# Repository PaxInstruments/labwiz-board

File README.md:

# Pax Instruments
# armwiz-board

[Pax Instruments Template Module](<link to store page>)

## Overview
The Pax Instruments armwiz board is a development board based on the STM32 series processors specifically targeting the STM32F103RxT series. You can [purchase this item in our store](http://paxinstruments.com/products/).

## Repository Contents
- __Datasheets__ - Datasheets for relevant components and parts
- __Electronics__ - All PCB and schematic design files
- __Enclosure__ - Enclosure 3D design files
- __Firmware__ - Firmware, libraries, and examples
- __Production__ - Manufacturing resources
- __Resources__ - Other resources

## Product Versions

## License Information
```
Place the license statement here
```

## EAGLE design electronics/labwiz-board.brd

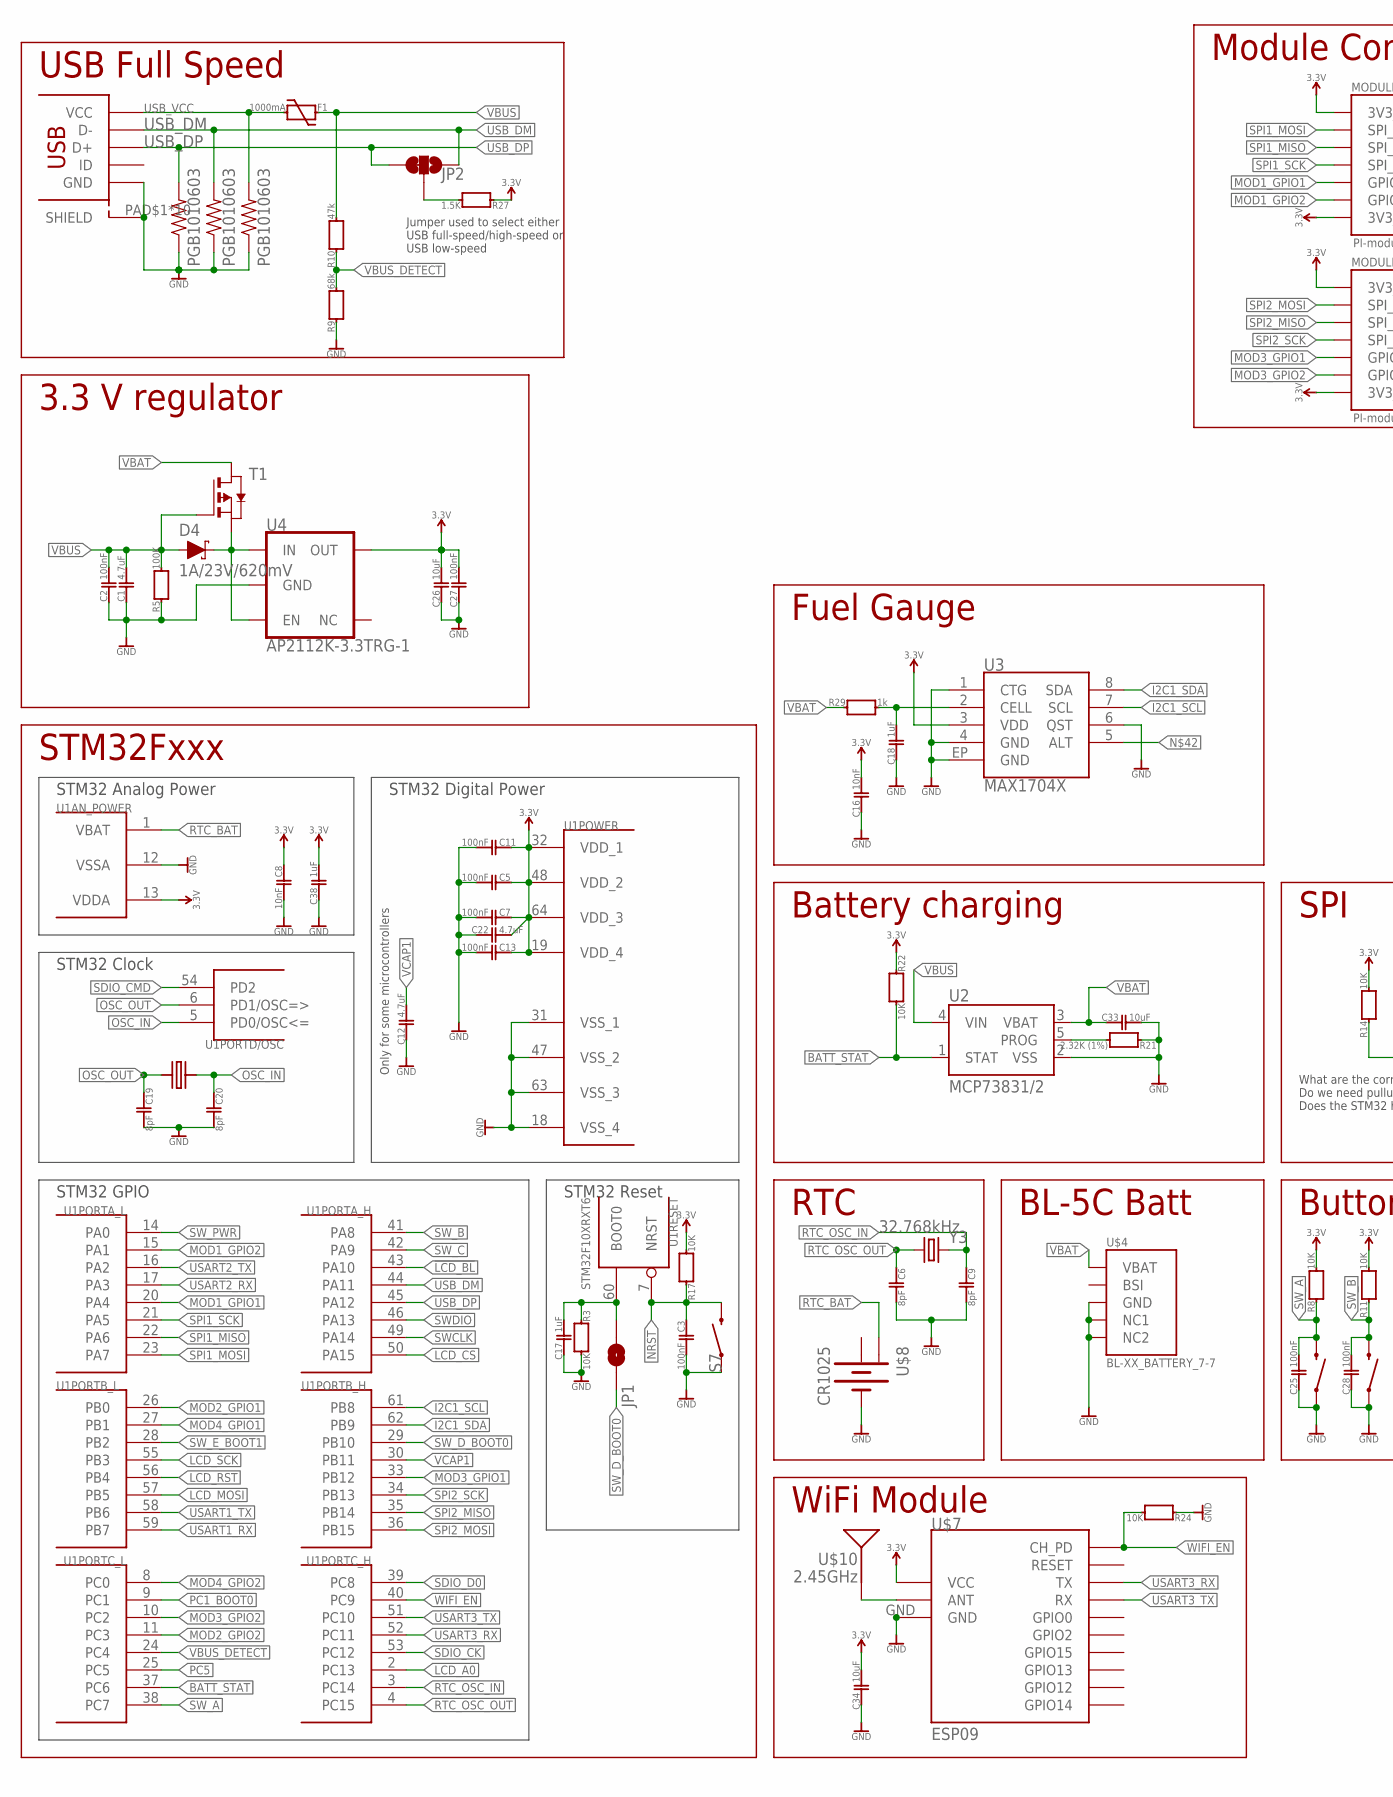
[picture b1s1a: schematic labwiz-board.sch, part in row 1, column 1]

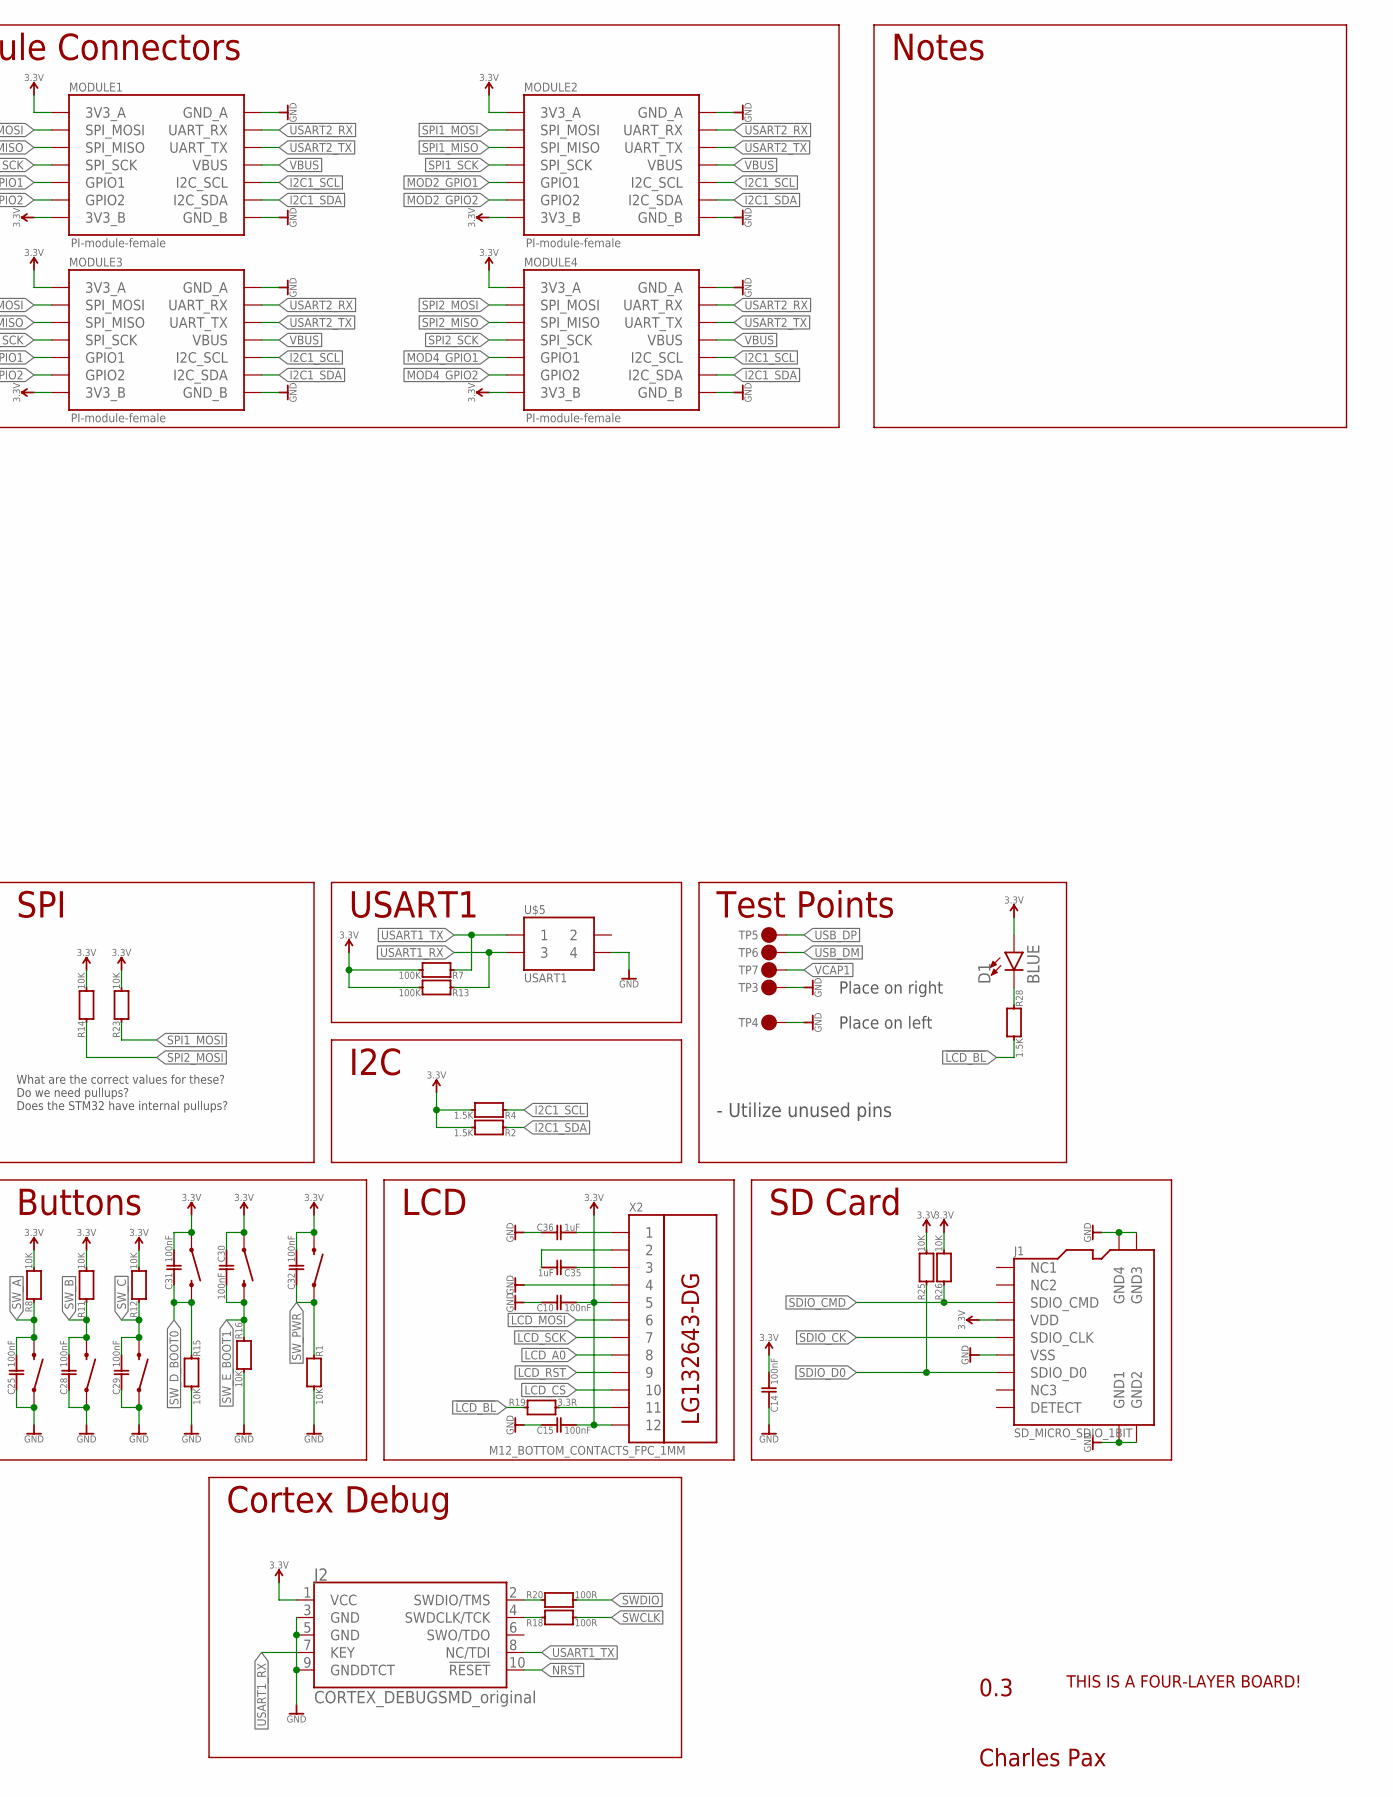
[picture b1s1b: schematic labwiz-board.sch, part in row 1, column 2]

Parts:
C1, C12, C22: 4.7uF; 0402
C2, C3, C5, C7, C10, C11, C13, C14, C15, C25, C27, C28, C29, C30, C31, C32: 100nF; 0402
C6, C9, C19, C20: 8pF; 0402
C8, C16: 10nF; 0402
C17, C18, C35, C36, C38: 1uF; 0402
C26, C33, C34: 10uF; 0402
D1: BLUE; LED-0603
D4: 1A/23V/620mV; SOD-323
F1: 1000mA; 0805
J1: SD_MICRO_SDIO_1BIT; SD_MICRO_1
J2: CORTEX_DEBUGSMD_original; SAMTECH_FTSH-105-01
JP1: DNP; PAD-JUMPER-2-NO_YES_SILK
JP2: JUMPER-SMT_3_1-NC_TRACE_SILK; SMT-JUMPER_3_1-NC_TRACE_SILK
MODULE1, MODULE2, MODULE3, MODULE4: PI-module-female; M07X2_2MM_EDGE
R1, R3, R8, R11, R12, R14, R15, R16, R17, R22, R23, R24, R25, R26: 10K; 0402
R2, R4, R27, R28: 1.5K; 0402
R5, R7, R13: 100K; 0402
R9: 68k; 0402
R10: 47k; 0402
R18, R20: 100R; 0402
R19: 3.3R; 0402
R21: 2.32K (1%); 0402
R29: 1k; 0402
S1, S2, S3, S4, S5, S6: SWITCH-MOMENTARY-2SMD; TACTILE_SWITCH_SMD; MPN RS-187R05A2-DS MT RT
S7: SWITCH-MOMENTARY-2SMD-3; TACTILE_SWITCH_SMD-3
T1: PMOSSOT23-6; SOT23-6
TP3, TP4: DNP; M01_TH
TP5, TP6, TP7: DNP; PAD_1MM
U1: STM32F10XRXT6; TQFP64
U2: MCP73831/2; SOT23-5
U3: MAX1704X; TDFN-8
U4: AP2112K-3.3TRG-1; SOT23-5
U$1: USB_MICROSMT+THRUHULE; USB_MICRO_THRUHOLE; MPN 10118194-0001LF
U$2: DNP; FOUR_LAYER_WARNING
U$3: LG132643-DG
U$4: BL-XX_BATTERY_7-7; BL-XX-BATTERY
U$5: USART1; M02X2_TH_RIGHT_ANGLE
U$7: ESP09
U$8: CR1025; CR2025
U$9: 8MHz; NX3225GD
U$10: 2.45GHz; ANT-2.4GHZ-6.5X2.2MM
X2: M12_BOTTOM_CONTACTS_FPC_1MM; FPC_12P_1MM
Y3: 32.768kHz; CRYSTAL-SMD-3.2X1.5MM
Z1, Z2, Z3: PGB1010603; SPARKFUN-RESISTORS_0603-RES; MPN PGB1010603NRHF

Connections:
3.3V: C5.1, C7.1, C8.1, C10.2, C11.1, C13.1, C14.2, C15.2, C16.2, C22.2, C26.2, C27.2, C30.1, C31.2, C32.2, C34.2, C38.2, D1.A, J1.4 (VDD), J2.1 (VCC), MODULE1.P$1 (3V3_A), MODULE1.P$13 (3V3_B), MODULE2.P$1 (3V3_A), MODULE2.P$13 (3V3_B), MODULE3.P$1 (3V3_A), MODULE3.P$13 (3V3_B), MODULE4.P$1 (3V3_A), MODULE4.P$13 (3V3_B), R2.1, R4.1, R7.1, R8.1, R11.1, R12.1, R13.1, R14.1, R17.1, R22.2, R23.1, R25.1, R26.1, R27.2, S4.1, S5.1, S6.3 (2), U1.13 (VDDA), U1.19 (VDD_4), U1.32 (VDD_1), U1.48 (VDD_2), U1.64 (VDD_3), U3.3 (VDD), U4.5 (OUT), U$7.VCC, X2.5, X2.12
!LCD_BL: R19.2, R28.1, U1.43 (PA10)
+: U$8.P$2 (+)
BATT_STAT: R22.1, U1.37 (PC6), U2.1 (STAT)
GND: C1.1, C2.1, C3.2, C5.2, C6.2, C7.2, C8.2, C9.2, C10.1, C11.2, C12.1, C13.2, C14.1, C15.1, C16.1, C17.1, C18.1, C19.2, C20.2, C22.1, C25.1, C26.1, C27.1, C28.1, C29.1, C33.2, C34.1, C36.1, C38.1, J1.6 (VSS), J1.G1 (GND1), J1.G2 (GND2), J1.G3 (GND3), J1.G4 (GND4), J2.3 (GND), J2.5 (GND), J2.9 (GNDDTCT), MODULE1.P$2 (GND_A), MODULE1.P$14 (GND_B), MODULE2.P$2 (GND_A), MODULE2.P$14 (GND_B), MODULE3.P$2 (GND_A), MODULE3.P$14 (GND_B), MODULE4.P$2 (GND_A), MODULE4.P$14 (GND_B), R1.1, R3.1, R5.2, R9.2, R15.1, R16.1, R21.2, R24.2, S1.1, S2.1, S3.1, S7.1, TP3.P$1, TP4.P$1, U1.12 (VSSA), U1.18 (VSS_4), U1.31 (VSS_1), U1.47 (VSS_2), U1.63 (VSS_3), U2.2 (VSS), U3.1 (CTG), U3.4 (GND), U3.6 (QST), U3.EP (GND), U4.2 (GND), U$1.PAD$1 (SHIELD), U$1.PAD$2 (SHIELD), U$1.PAD$3 (SHIELD), U$1.PAD$4 (SHIELD), U$1.PAD$5 (SHIELD), U$1.PAD$6 (SHIELD), U$1.PAD$7 (SHIELD), U$1.PAD$8 (SHIELD), U$1.PAD$9 (SHIELD), U$1.PAD$10 (SHIELD)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
I2C1_SCL: MODULE1.P$10 (I2C_SCL), MODULE2.P$10 (I2C_SCL), MODULE3.P$10 (I2C_SCL), MODULE4.P$10 (I2C_SCL), R4.2, U1.61 (PB8), U3.7 (SCL)
I2C1_SDA: MODULE1.P$12 (I2C_SDA), MODULE2.P$12 (I2C_SDA), MODULE3.P$12 (I2C_SDA), MODULE4.P$12 (I2C_SDA), R2.2, U1.62 (PB9), U3.8 (SDA)
LCD_A0: U1.2 (PC13), X2.8
LCD_CS: U1.50 (PA15), X2.10
LCD_MOSI: U1.57 (PB5), X2.6
LCD_RST: U1.56 (PB4), X2.9
LCD_SCK: U1.55 (PB3), X2.7
MOD1_GPIO1: MODULE1.P$9 (GPIO1), U1.20 (PA4)
MOD1_GPIO2: MODULE1.P$11 (GPIO2), U1.15 (PA1)
MOD2_GPIO1: MODULE2.P$9 (GPIO1), U1.26 (PB0)
MOD2_GPIO2: MODULE2.P$11 (GPIO2), U1.11 (PC3)
MOD3_GPIO1: MODULE3.P$9 (GPIO1), U1.33 (PB12)
MOD3_GPIO2: MODULE3.P$11 (GPIO2), U1.10 (PC2)
MOD4_GPIO1: MODULE4.P$9 (GPIO1), U1.27 (PB1)
MOD4_GPIO2: MODULE4.P$11 (GPIO2), U1.8 (PC0)
unnamed: R19.1, X2.11
unnamed: JP2.2, R27.1
unnamed: U$7.ANT, U$10.FEED
unnamed: C18.2, R29.1, U3.2 (CELL)
unnamed: D1.C, R28.2
unnamed: D4.C, T1.4 (S), U4.1 (IN), U4.3 (EN)
unnamed: C35.1, X2.3
unnamed: C35.2, X2.2
unnamed: C36.2, X2.1
unnamed: R21.1, U2.5 (PROG)
NRST: C3.1, J2.10 (!RESET), R17.2, S7.4 (2), U1.7 (NRST)
OSC_IN: C20.1, U1.5 (PD0/OSC<=), U$9.P$2
OSC_OUT: C19.1, U1.6 (PD1/OSC=>), U$9.P$1
PC1_BOOT0: C17.2, JP1.2, R3.2, U1.9 (PC1), U1.60 (BOOT0)
PC5: U1.25 (PC5)
RTC_BAT: U1.1 (VBAT), U$8.P$3 (+1)
RTC_OSC_IN: C9.1, U1.3 (PC14), Y3.P$2 (2)
RTC_OSC_OUT: C6.1, U1.4 (PC15), Y3.P$1 (1)
SDIO_CK: J1.5 (SDIO_CLK), U1.53 (PC12)
SDIO_CMD: J1.3 (SDIO_CMD), R26.2, U1.54 (PD2)
SDIO_D0: J1.7 (SDIO_D0), R25.2, U1.39 (PC8)
SPI1_MISO: MODULE1.P$5 (SPI_MISO), MODULE2.P$5 (SPI_MISO), U1.22 (PA6)
SPI1_MOSI: MODULE1.P$3 (SPI_MOSI), MODULE2.P$3 (SPI_MOSI), R23.2, U1.23 (PA7)
SPI1_SCK: MODULE1.P$7 (SPI_SCK), MODULE2.P$7 (SPI_SCK), U1.21 (PA5)
SPI2_MISO: MODULE3.P$5 (SPI_MISO), MODULE4.P$5 (SPI_MISO), U1.35 (PB14)
SPI2_MOSI: MODULE3.P$3 (SPI_MOSI), MODULE4.P$3 (SPI_MOSI), R14.2, U1.36 (PB15)
SPI2_SCK: MODULE3.P$7 (SPI_SCK), MODULE4.P$7 (SPI_SCK), U1.34 (PB13)
SWCLK: R18.1, U1.49 (PA14)
SWDCLK_M: J2.4 (SWDCLK/TCK), R18.2
SWDIO: R20.1, U1.46 (PA13)
SWDIO_M: J2.2 (SWDIO/TMS), R20.2
SW_A: C25.2, R8.2, S3.3 (2), U1.38 (PC7)
SW_B: C28.2, R11.2, S2.3 (2), U1.41 (PA8)
SW_C: C29.2, R12.2, S1.3 (2), U1.42 (PA9)
SW_D_BOOT0: C31.1, JP1.1, R15.2, S4.3 (2), U1.29 (PB10)
SW_E_BOOT1: C30.2, R16.2, S5.3 (2), U1.28 (PB2)
SW_PWR: C32.1, R1.2, S6.1, U1.14 (PA0)
USART1_RX: J2.7 (KEY), R13.2, U1.59 (PB7), U$5.3
USART1_TX: J2.8 (NC/TDI), R7.2, U1.58 (PB6), U$5.1
USART2_RX: MODULE1.P$4 (UART_RX), MODULE2.P$4 (UART_RX), MODULE3.P$4 (UART_RX), MODULE4.P$4 (UART_RX), U1.17 (PA3)
USART2_TX: MODULE1.P$6 (UART_TX), MODULE2.P$6 (UART_TX), MODULE3.P$6 (UART_TX), MODULE4.P$6 (UART_TX), U1.16 (PA2)
USART3_RX: U1.52 (PC11), U$7.TX
USART3_TX: U1.51 (PC10), U$7.RX
USB_DM: JP2.1, TP6.P$1, U1.44 (PA11), U$1.PIN$2 (D-), Z2.2
USB_DP: JP2.3, TP5.P$1, U1.45 (PA12), U$1.PIN$3 (D+), Z1.2
USB_VCC: F1.1, U$1.PIN$1 (VCC), Z3.2
VBAT: C33.1, R29.2, T1.1 (D), T1.2 (D), T1.5 (D), T1.6 (D), U2.3 (VBAT), U$4.P$1 (VBAT)
VBUS: C1.2, C2.2, D4.A, F1.2, MODULE1.P$8 (VBUS), MODULE2.P$8 (VBUS), MODULE3.P$8 (VBUS), MODULE4.P$8 (VBUS), R5.1, R10.1, T1.3 (G), U2.4 (VIN)
VBUS_DETECT: R9.1, R10.2, U1.24 (PC4)
VCAP1: C12.2, TP7.P$1, U1.30 (PB11)
WIFI_EN: R24.1, U1.40 (PC9), U$7.CH_PD

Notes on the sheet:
USB Full Speed
3.3 V regulator
LCD
Buttons
0.3
Charles Pax
SD Card
STM32 Digital Power
STM32 Analog Power
STM32 Clock
STM32 Reset
STM32Fxxx
STM32 GPIO
RTC
Module Connectors
BL-5C Batt
Cortex Debug
WiFi Module
Battery charging
USART1
Notes
- Utilize unused pins
Only for some microcontrollers
I2C
Test Points
Place on left
Place on right
Jumper used to select either USB full-speed/high-speed or USB low-speed
SPI
What are the correct values for these? Do we need pullups? Does the STM32 have internal pullups?
Fuel Gauge

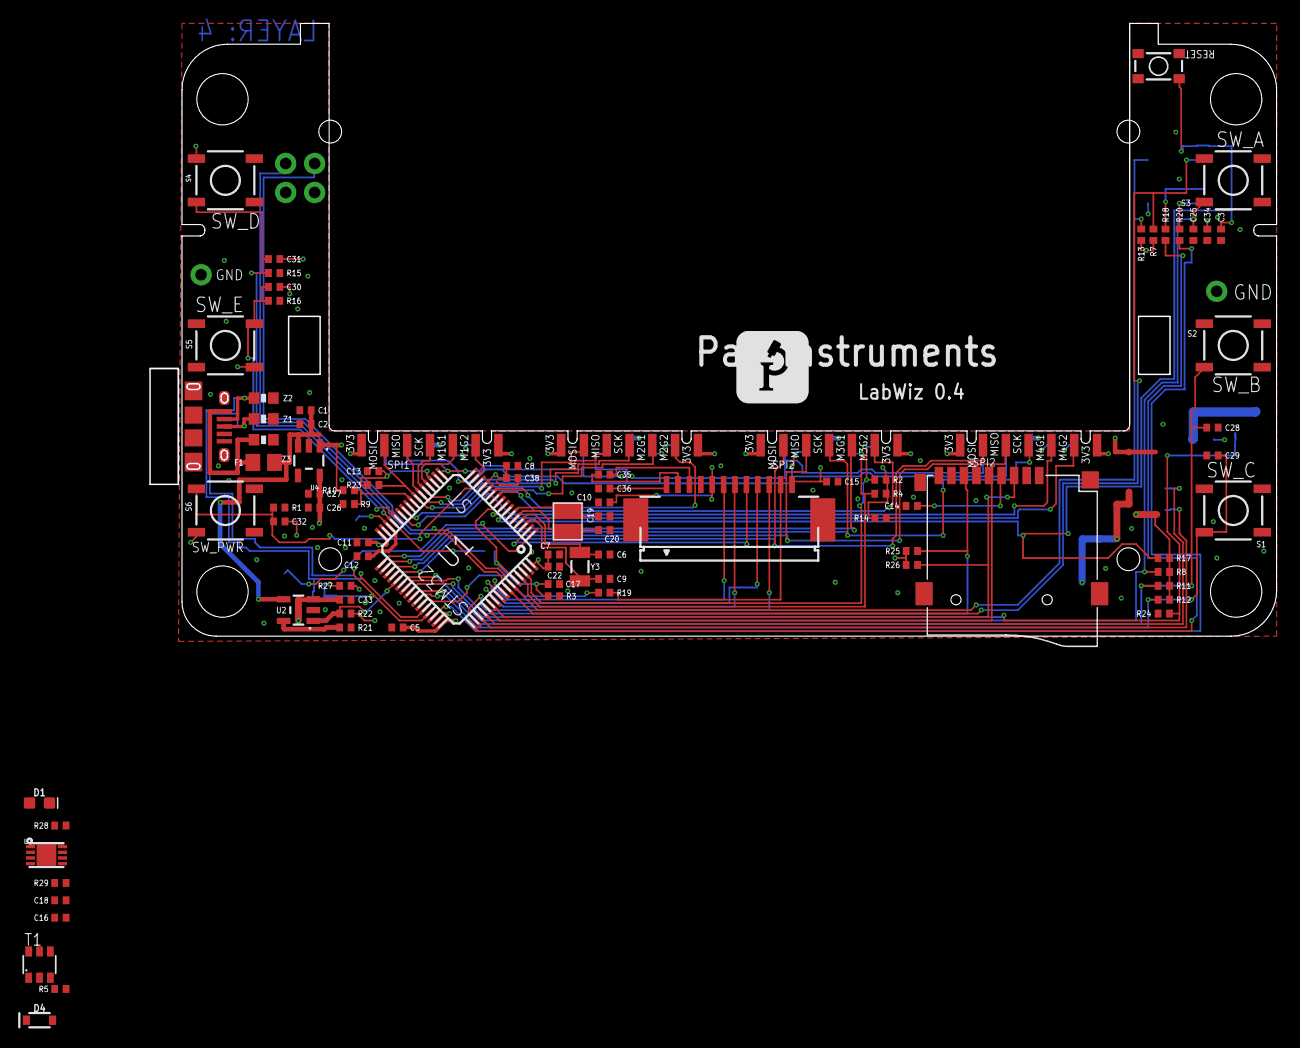
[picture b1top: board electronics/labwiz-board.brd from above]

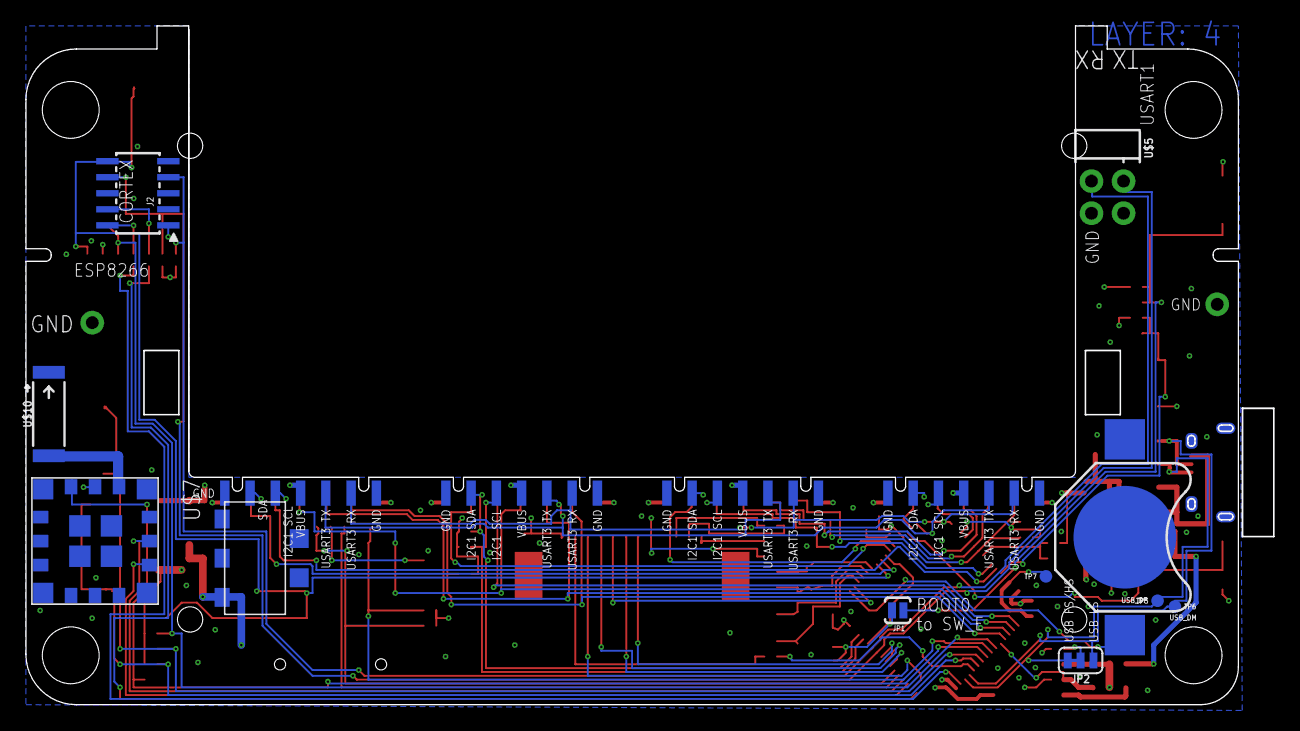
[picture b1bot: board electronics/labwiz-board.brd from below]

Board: 4 copper layers, 98.8 x 53.7 mm, 104 parts (11 on the bottom side), 69 nets.

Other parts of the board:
U$6: PAX-LOGO-0.25IN

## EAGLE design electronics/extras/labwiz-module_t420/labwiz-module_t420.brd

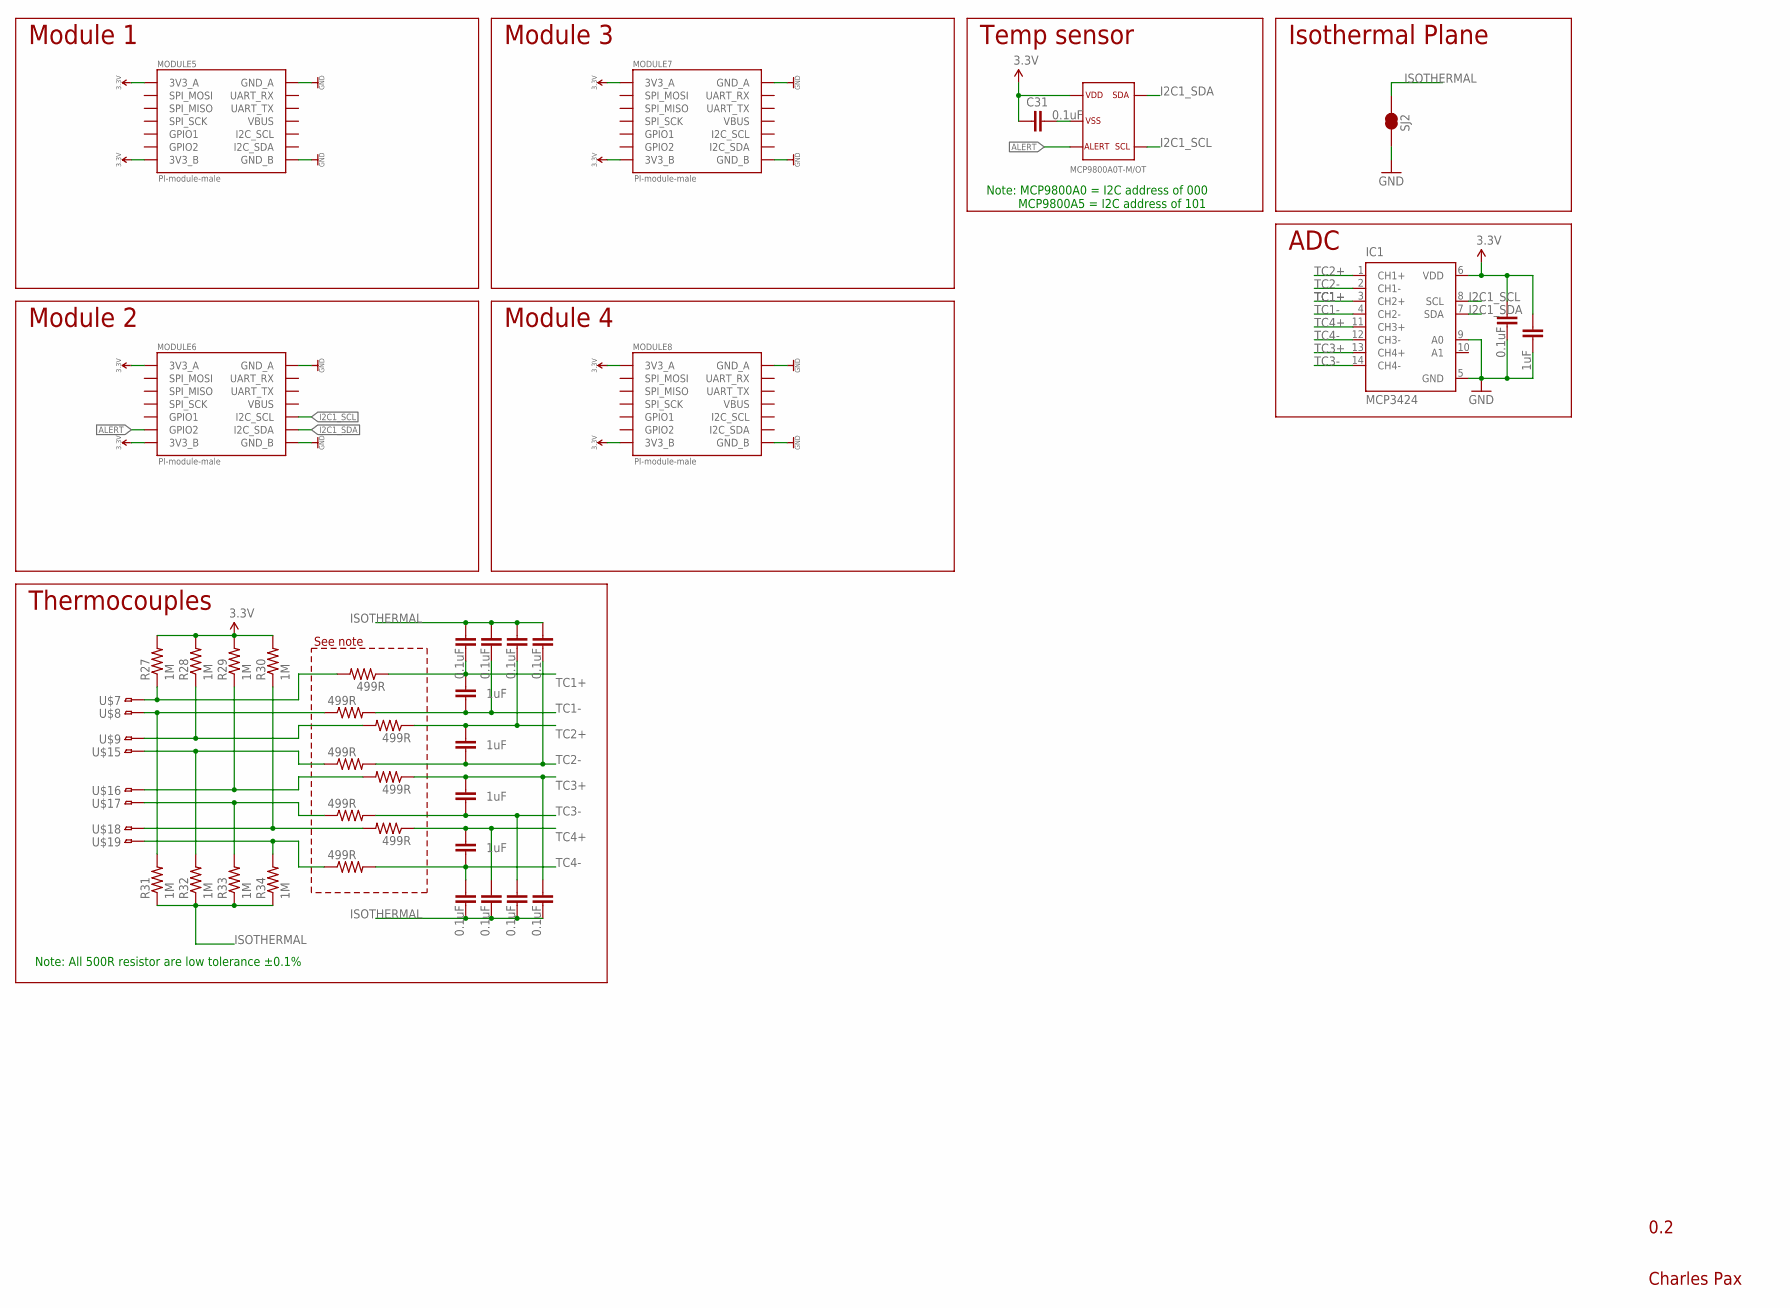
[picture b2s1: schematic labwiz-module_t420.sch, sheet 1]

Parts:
C7, C8, C10, C11, C30: 1uF; SPARKFUN-CAPACITORS_0603-CAP
C13, C14, C15, C16, C17, C24, C25, C29, C31, C37: 0.1uF; SPARKFUN-CAPACITORS_0603-CAP
IC1: MCP3424; SO14; MPN MCP3424-E/SL
MODULE5, MODULE6, MODULE7, MODULE8: PI-module-male; M07X2_2MM_EDGE
R27, R28, R29, R30, R31, R32, R33, R34: 1M; SPARKFUN-RESISTORS_0603-RES
R35, R36, R37, R38, R39, R40, R41, R42: 499R; SPARKFUN-RESISTORS_0603-RES; MPN TNPW0603499RBEEA
SJ2: JUMPER-PAD-2-NC_BY_TRACE; PAD-JUMPER-2-NC_BY_TRACE_YES_SILK; MPN N/A
U1: MCP9800; SOT23-5L; MPN MCP9800A0T-M/OT
U$7, U$8, U$9, U$15, U$16, U$17, U$18, U$19: TC-MINI-SINGLE; TC-CLIP-SINGLE

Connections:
3.3V: C29.1, C30.1, C31.1, IC1.6 (VDD), MODULE5.P$1 (3V3_B), MODULE5.P$13 (3V3_A), MODULE6.P$1 (3V3_B), MODULE6.P$13 (3V3_A), MODULE7.P$1 (3V3_B), MODULE7.P$13 (3V3_A), MODULE8.P$1 (3V3_B), MODULE8.P$13 (3V3_A), R27.2, R28.2, R29.2, R30.2, U1.1
ALERT: MODULE6.P$3 (GPIO2), U1.3
GND: C29.2, C30.2, IC1.5 (GND), IC1.9 (A0), MODULE5.P$2 (GND_B), MODULE5.P$14 (GND_A), MODULE6.P$2 (GND_B), MODULE6.P$14 (GND_A), MODULE7.P$2 (GND_B), MODULE7.P$14 (GND_A), MODULE8.P$2 (GND_B), MODULE8.P$14 (GND_A), SJ2.1
I2C1_SCL: IC1.8 (SCL), MODULE6.P$6 (I2C_SCL), U1.4
I2C1_SDA: IC1.7 (SDA), MODULE6.P$4 (I2C_SDA), U1.5
ISOTHERMAL: C13.2, C14.2, C15.2, C16.2, C17.1, C24.1, C25.1, C31.2, C37.1, R31.1, R32.1, R33.1, R34.1, SJ2.2, U1.2
unnamed: R27.1, R35.2, U$7.P$1
unnamed: R32.2, R38.1, U$15.P$1
unnamed: R31.2, R36.1, U$8.P$1
unnamed: R28.1, R37.2, U$9.P$1
unnamed: R30.1, R40.2, U$18.P$1
unnamed: R29.1, R39.2, U$16.P$1
unnamed: R33.2, R41.1, U$17.P$1
unnamed: R34.2, R42.1, U$19.P$1
TC1+: C7.1, C17.2, IC1.3 (CH2+), R35.1
TC1-: C7.2, C24.2, IC1.4 (CH2-), R36.2
TC2+: C8.1, C25.2, IC1.1 (CH1+), R37.1
TC2-: C8.2, C37.2, IC1.2 (CH1-), R38.2
TC3+: C10.1, C16.1, IC1.13 (CH4+), R39.1
TC3-: C10.2, C15.1, IC1.14 (CH4-), R41.2
TC4+: C11.1, C14.1, IC1.11 (CH3+), R40.1
TC4-: C11.2, C13.1, IC1.12 (CH3-), R42.2

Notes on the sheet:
0.2
Charles Pax
Module 1
Module 2
Module 3
Module 4
Temp sensor
Note: MCP9800A0 = I2C address of 000 MCP9800A5 = I2C address of 101
ADC
Isothermal Plane
Thermocouples
Note: All 500R resistor are low tolerance ±0.1%
See note

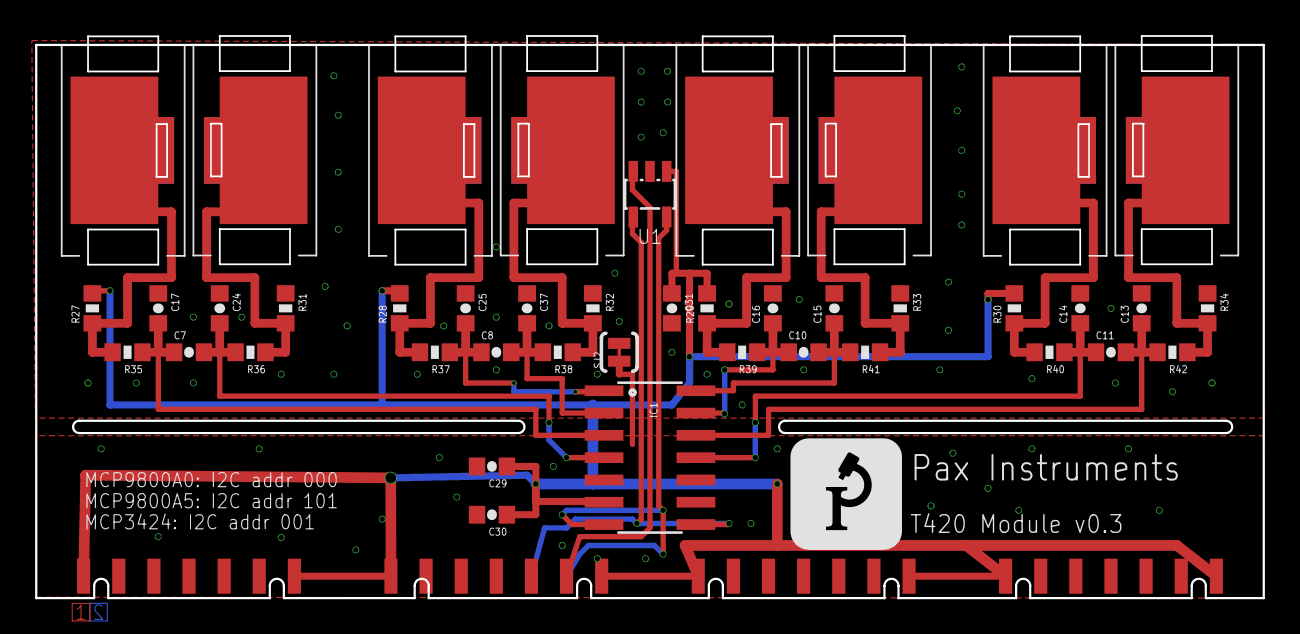
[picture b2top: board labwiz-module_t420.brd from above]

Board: 4 copper layers, 69.9 x 32.0 mm, 48 parts (0 on the bottom side), 22 nets.

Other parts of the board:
U$1: PAX-LOGO-0.25IN
U$2: LAYERS-LABEL-2

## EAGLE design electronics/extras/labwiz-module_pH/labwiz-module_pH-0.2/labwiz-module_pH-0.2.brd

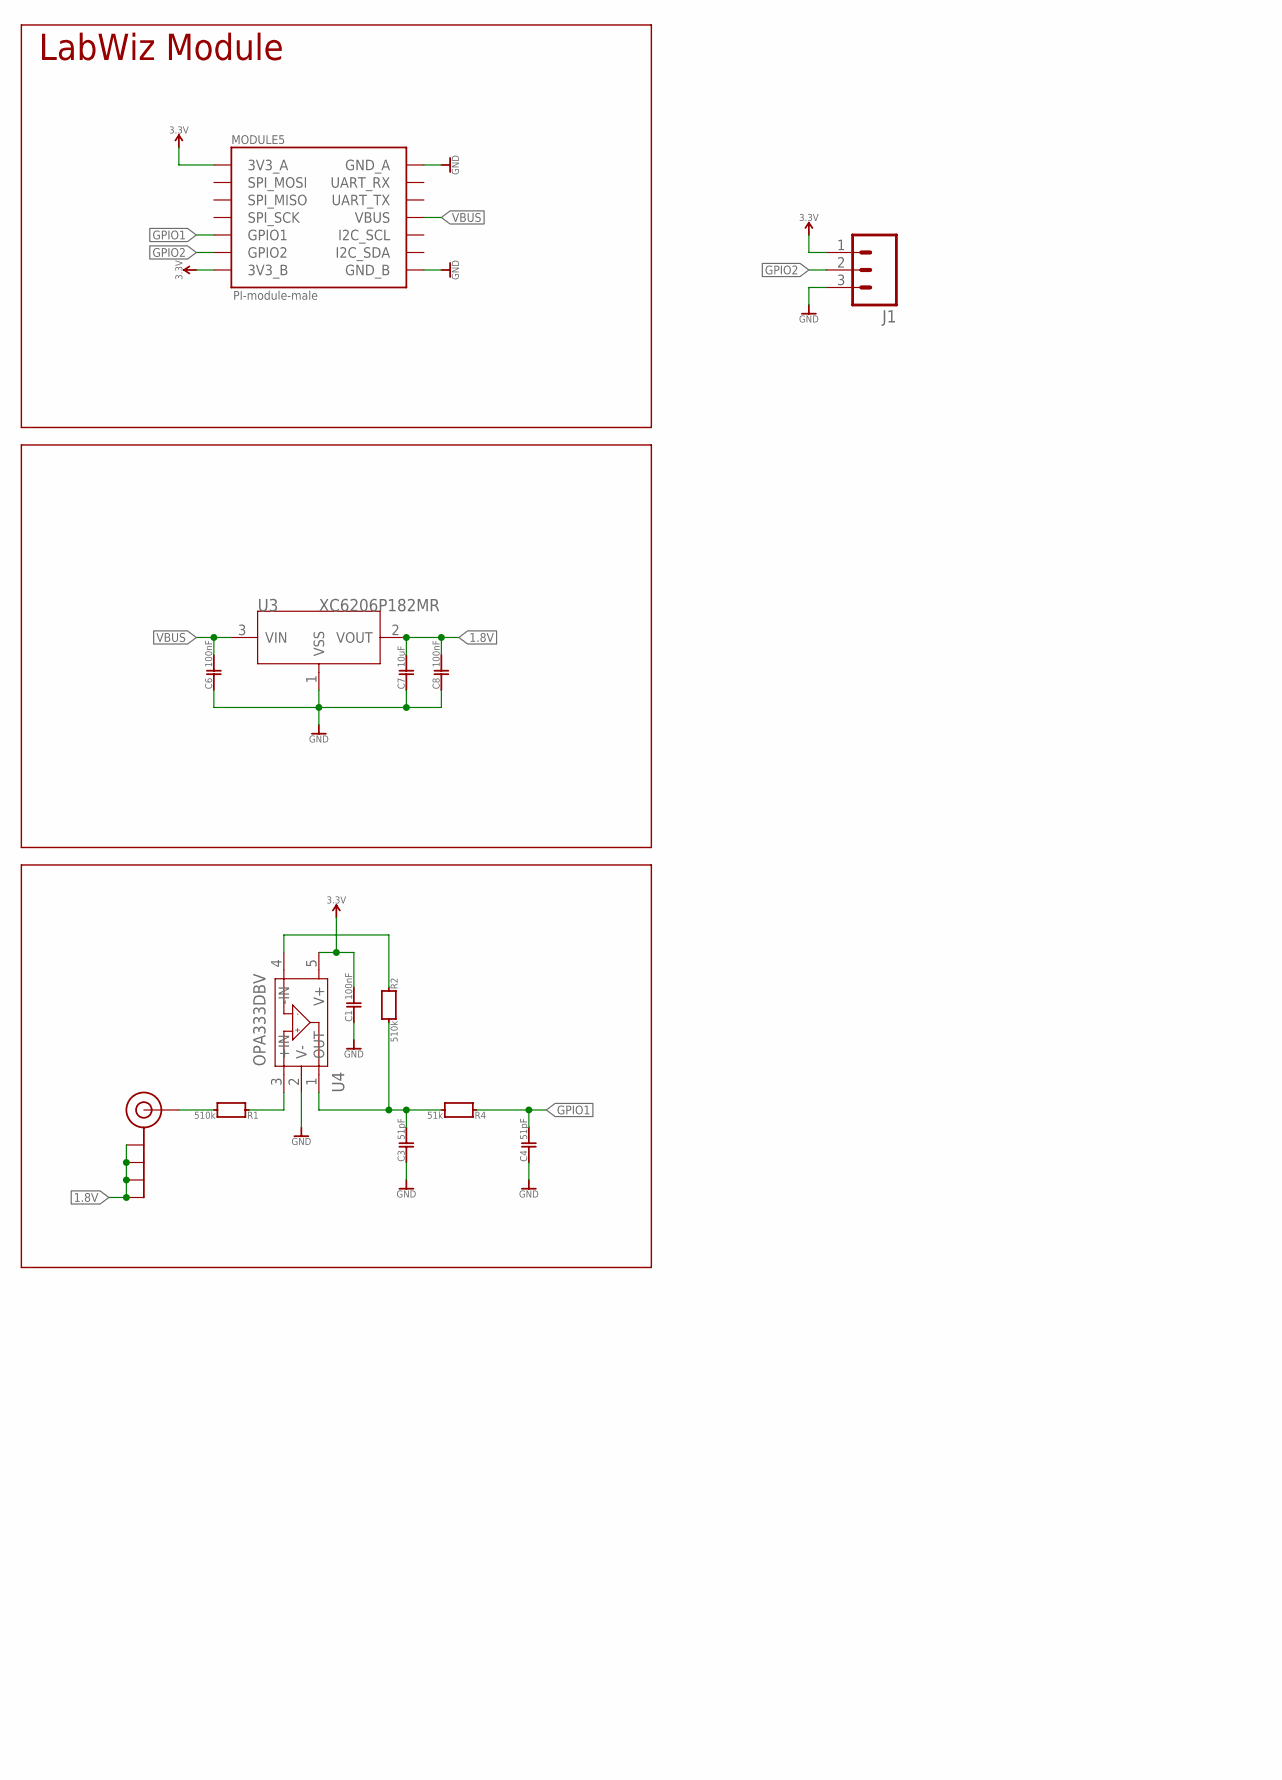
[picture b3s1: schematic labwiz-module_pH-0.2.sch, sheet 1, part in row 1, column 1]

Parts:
C1, C6, C8: 100nF; 0603
C3, C4: 51pF; 0603
C7: 10uF; 0603
J1: M03LOCK_LONGPADS; 1X03_LOCK_LONGPADS
J$1: SMA_EDGE; SMA-EDGE
MODULE5: PI-module-male; M07X2_2MM_EDGE
R1, R2: 510k; 0603
R4: 51k; 0603
U3: XC6206P182MR; SOT23
U4: OPA333DBV; SOT23-5

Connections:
1.8V: C7.2, C8.2, J$1.GND@0 (GND), J$1.GND@1 (GND), J$1.GND@2 (GND), J$1.GND@3 (GND), U3.2 (VOUT)
3.3V: C1.2, J1.1, MODULE5.P$1 (3V3_B), MODULE5.P$13 (3V3_A), U4.5 (V+)
GND: C1.1, C3.1, C4.1, C6.1, C7.1, C8.1, J1.3, MODULE5.P$2 (GND_B), MODULE5.P$14 (GND_A), U3.1 (VSS), U4.2 (V-)
GPIO1: C4.2, MODULE5.P$5 (GPIO1), R4.2
GPIO2: J1.2, MODULE5.P$3 (GPIO2)
unnamed: J$1.SIG (SIGNAL), R1.1
unnamed: R1.2, U4.3 (+IN)
unnamed: R2.2, U4.4 (-IN)
unnamed: C3.2, R2.1, R4.1, U4.1 (OUT)
VBUS: C6.2, MODULE5.P$8 (VBUS), U3.3 (VIN)

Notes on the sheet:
0.2
Charles Pax
LabWiz Module

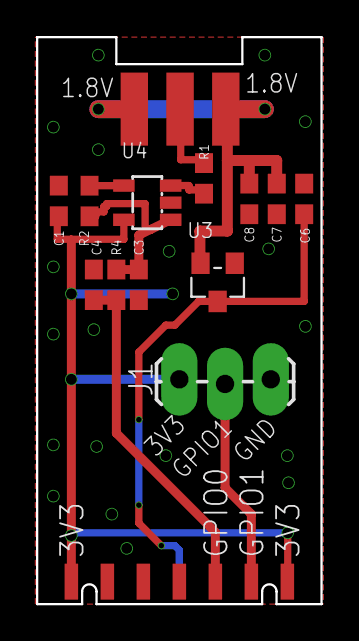
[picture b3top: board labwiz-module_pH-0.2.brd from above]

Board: 4 copper layers, 15.8 x 31.5 mm, 14 parts (0 on the bottom side), 10 nets.

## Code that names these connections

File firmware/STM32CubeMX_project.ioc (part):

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Mcu.Name=STM32F103R(F-G)Tx
Mcu.Package=LQFP64
Mcu.UserName=STM32F103RGTx
PA0-WKUP.Mode=SYS_WakeUp0
PA0-WKUP.Signal=SYS_WKUP
PA1.GPIOParameters=GPIO_Label
PA1.GPIO_Label=MOD2_GPIO0
PA1.Signal=GPIO_Analog
PA10.Mode=Asynchronous
PA10.Signal=USART1_RX
PA11.Mode=Device
PA11.Signal=USB_DM
PA12.Mode=Device
PA12.Signal=USB_DP
PA13.Mode=Serial_Wire
PA13.Signal=SYS_JTMS-SWDIO
PA14.Mode=Serial_Wire
PA14.Signal=SYS_JTCK-SWCLK
PA15.GPIOParameters=GPIO_Label
PA15.GPIO_Label=SPI3_NSS (LCD_CS)
PA15.Mode=NSS_Signal_Hard_Output
PA15.Signal=SPI3_NSS
PA2.Mode=Asynchronous
PA2.Signal=USART2_TX
PA3.Mode=Asynchronous
PA3.Signal=USART2_RX
PA4.Mode=NSS_Signal_Hard_Output
PA4.Signal=SPI1_NSS
PA5.Mode=Full_Duplex_Master
PA5.Signal=SPI1_SCK
PA6.Mode=Full_Duplex_Master
PA6.Signal=SPI1_MISO
PA7.Mode=Full_Duplex_Master
PA7.Signal=SPI1_MOSI
PA8.GPIOParameters=GPIO_Label
PA8.GPIO_Label=SW_D
PA8.Signal=GPXTI8
PA9.Mode=Asynchronous
PA9.Signal=USART1_TX
PB0.GPIOParameters=GPIO_Label
PB0.GPIO_Label=VBAP_1/2
PB0.Signal=GPIO_Analog
PB1.GPIOParameters=GPIO_Label
PB1.GPIO_Label=MOD4_GPIO1
PB1.Signal=GPIO_Analog
PB10.Mode=I2C
PB10.Signal=I2C2_SCL
PB11.Mode=I2C
PB11.Signal=I2C2_SDA
PB12.Mode=NSS_Signal_Hard_Output
PB12.Signal=SPI2_NSS
PB13.Mode=Full_Duplex_Master
PB13.Signal=SPI2_SCK
PB14.Mode=Full_Duplex_Master
PB14.Signal=SPI2_MISO
PB15.Mode=Full_Duplex_Master
PB15.Signal=SPI2_MOSI
PB2.GPIOParameters=GPIO_Label
PB2.GPIO_Label=SW_E(BOOT1)
PB2.Signal=GPXTI2
PB3.GPIOParameters=GPIO_Label
PB3.GPIO_Label=SPI3_SCK(LCD_SCK)
PB3.Mode=Simplex_Bidirectional_Master
PB3.Signal=SPI3_SCK
PB4.GPIOParameters=GPIO_Label
PB4.GPIO_Label=LCD_BL
PB4.Signal=GPIO_Output
PB5.GPIOParameters=GPIO_Label
PB5.GPIO_Label=SPI3_MOSI(LCD_MOSI)
PB5.Mode=Simplex_Bidirectional_Master
PB5.Signal=SPI3_MOSI
PB6.Mode=I2C
PB6.Signal=I2C1_SCL
PB7.Mode=I2C
PB7.Signal=I2C1_SDA
PB8.Mode=Master
PB8.Signal=CAN_RX
PB9.Mode=Master
PB9.Signal=CAN_TX
PC0.GPIOParameters=GPIO_Label
PC0.GPIO_Label=GPIO_Output (LCD_A0)
PC0.Signal=GPIO_Output
PC1.GPIOParameters=GPIO_Label
PC1.GPIO_Label=GPIO_Output (SD_DETECT)
PC1.Signal=GPIO_Output
PC10.GPIOParameters=GPIO_Label
PC10.GPIO_Label=SW_B
PC10.Signal=GPXTI10
PC11.GPIOParameters=GPIO_Label
PC11.GPIO_Label=SW_A
PC11.Signal=GPXTI11
PC12.Mode=SD_1_bit
PC12.Signal=SDIO_CK
PC13-TAMPER-RTC.GPIOParameters=GPIO_Label
PC13-TAMPER-RTC.GPIO_Label=GPIO_Output (LCD_RST)
PC13-TAMPER-RTC.Signal=GPIO_Output
PC14-OSC32_IN.Mode=LSE-External-Oscillator
PC14-OSC32_IN.Signal=RCC_OSC32_IN
PC15-OSC32_OUT.Mode=LSE-External-Oscillator
PC15-OSC32_OUT.Signal=RCC_OSC32_OUT
PC2.GPIOParameters=GPIO_Label
PC2.GPIO_Label=MOD3_GPIO1
PC2.Signal=GPIO_Analog
PC3.GPIOParameters=GPIO_Label
PC3.GPIO_Label=MOD2_GPIO1
PC3.Signal=GPIO_Analog
PC4.GPIOParameters=GPIO_Label
PC4.GPIO_Label=MOD1_GPIO1
PC4.Signal=GPIO_Analog
PC5.GPIOParameters=GPIO_Label
PC5.GPIO_Label=MOD4_GPIO0
PC5.Signal=GPIO_Analog
PC6.Signal=GPIO_Output
PC7.GPIOParameters=GPIO_Label
PC7.GPIO_Label=SW_C
PC7.Signal=GPXTI7
PC8.Mode=SD_1_bit
PC8.Signal=SDIO_D0
PC9.GPIOParameters=GPIO_Label
PC9.GPIO_Label=VBUS
PC9.Signal=GPIO_Analog
PD0-OSC_IN.Mode=HSE-External-Oscillator
PD0-OSC_IN.Signal=RCC_OSC_IN
PD1-OSC_OUT.Mode=HSE-External-Oscillator
PD1-OSC_OUT.Signal=RCC_OSC_OUT
PD2.Mode=SD_1_bit
PD2.Signal=SDIO_CMD
RCC.HSEDivPLL=RCC_HSE_PREDIV_DIV2
RCC.HSE_VALUE=16000000
RCC.SYSCLKFreq_VALUE=72000000
RCC.SYSCLKSource=RCC_SYSCLKSOURCE_PLLCLK

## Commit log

2016-02-26 Adding board design. Still working.
2016-02-26 Removed JTAG and ST-Link connectors. Added ARM Cortex Debug connector.
2016-02-26 Readded the ST Link connection. I'll try to keep them both.
2016-02-27 Cleaned up the schematic. No electrical changes.
2016-02-27 Copied labels for all the pins that need to be connected to the MCU.
2016-02-27 Added some traces. Just starting layout to see the general areas things should be. Then I can determine where the LCD and other items should be connected to the MCU.
2016-02-28 Routing and layout.
2016-02-28 More routing.
2016-04-30 Unknown modification.
2016-05-14 Made some changes to schematic.
2016-05-14 Did some routing.
2016-05-15 Basic layout done. Need to dome some details.
2016-05-15 Getting closer.
2016-05-16 Maybe something else.
2016-05-16 Moved some traces. Have a little more room now.
2016-05-17 reconfigured routing. Looks much better.
2016-05-18 Plugging along.
2016-05-19 Really close now.
2016-05-19 Four more wires.
2016-05-19 Added datasheets. This might be the final board layout and routing. Waiting on feedback.
2016-05-19 Moved some stuff in the schematic.
2016-05-19 Fixed MEMS oscillator issue. Closes #3.
2016-05-20 Added .gitignore file.
2016-05-20 Board passes ERC and DRC.
2016-05-20 Added CAM file.
2016-05-20 Added a Black Magic debugger to the prototyping area. This is not in the schematic and can be deleted.
2016-05-20 Added a directory for v0.1 design and gerber files.
2016-05-20 Removed Black Magic probe from design file.
2016-05-20 Added the DirtyPCBs.com render images.
2016-05-20 Added a 4 layer CAM file.
2016-05-20 Processed v0.1 with the 4 layer CAM file.
2016-05-21 Fixed an issue. Traces were going through the LCD cutout.
2016-05-21 Changed version v0.1.1
2016-05-29 Changed to a metric layout. Moved to a 7x2 2.0mm module connector.
2016-05-29 Added a STM32CubeMX project file. This defines the pins.
2016-05-30 Updated board with new Pax Instruments library parts.
2016-05-31 Signals routed to the module headers.
2016-05-31 Crazy routing work.
2016-06-01 Routed. Passes DRC. Added a thermocouple module.
2016-07-14 Changed serial pins on Cortex header. Added SWO to Cortex header. Added TODO notes to schematic.
2016-07-14 Added STM32 reference manual
2016-07-14 Added pogo pin pads for SWD.
2016-07-14 Added ESP8266 module footprint.
2016-07-14 Connected BOOT0 to SW_D. SW_D is default low voltage.
2016-07-14 Added the older gerber files.
2016-07-21 Added Seeed Studio Grove adapter modules. Now we can develop with Grove modules rather than design our own.
2016-07-22 Renamed files from armwiz to labwiz. Moved old version files to versions folder.
2016-08-05 Added a header for USART1 Rx Tx.
2016-08-08 Added pin docs to silk.
2016-08-08 Moved USART1. Added USART1 pullup resistors.
2016-08-08 Added pullup to RESET.
2016-08-08 Added solder jumper for BOOT0. Closes #22.
2016-08-08 Added RESET switch.
2016-08-08 Added BOOT0 jumper label. Added 100 nF caps to debounce switches.
2016-08-08 Swapped 8 MHz crystal for a commong footprint in HQB.
2016-08-08 Removed SWD pogo pads. Use the Cortex header or or pogo pins on the header pads.
2016-08-08 Removed SD_DETECT to use for BATT_STAT. Ran VBAT across board via 3V3 layer.
2016-08-15 Added power cap to WIFI. Added pulldown to WIFI_EN.
2016-08-15 Added CAN transciever. Routed. Passes DRC.
2016-08-15 Changed CAM file for larger clearance. Rerouted some items. CAN transceiver installed. Added component names to silkscreen.
2016-08-16 Added labwiz-0.2 files. Boards ordered.
2016-08-16 Added module templates.
2016-08-16 Single module is now consistent.
2016-08-16 Added a dual servo module.
2016-08-17 Added a pH module.
2016-08-20 Removed firmware directory.
2016-08-20 Removed all modules in labwiz board. The PCB house charges more than twice as much for a panelized design. This will also keep the BoM clean.
2016-08-20 Fixed silkscreen on module connectors.
2016-08-20 Moved modules into folders.
2016-08-20 Made board files for each module. Ordered boards.
2016-08-21 Widened the full module to 66 mm. Added a T420 module, which is just the sensor parts from a T400.
2016-08-22 All caps and resistors are now based on the updated Pax Instruments library.
2016-08-22 Modivied power capacitor values. See issue 45.
2016-08-22 Added 1.5k pullup resistors to all i2c lines.
2016-08-22 Updated components. CAN pin names are correct.
2016-09-06 Remapped pins. Routing...
2016-09-08 Switched some pins. Routed a bunch of the board.
2016-09-08 More routing...
2016-09-08 DRC pass. Must work on silkscreen now.
2016-09-09 Could be the final routing.
2016-09-09 Getting ready for gerber generation.
2016-09-10 Labwiz T420 module gerbers generated.
2016-09-13 Minor changes after design review. Will begin generating new gerbrs.
2016-09-13 Added gerbers and PDF for updated v0.3 board.
2016-09-14 Added schematic PDF for modules.
2016-09-14 Changed the connector locating slots from a milled slot to simply using the board outline. Now passes HQPCB test.
2016-09-15 Updated full-breakout and T420 modules. Boards ordered.
2016-09-15 Ordered new pH modules.
2016-09-15 Fixed VBUS issues on pH module.
2016-09-22 Small changes. Not sure what.
2016-12-11 Updated .gitignore. Comitting unknown schematic updates.
2016-12-11 Updated MCP73831/2 name.
2017-01-22 Swapped the net names for SW_D and SW_E. The physical locations were swapped on the v0.3 board.
2017-01-22 Added a pin map spreadsheet.
2017-01-22 Added interrupt information to pin map.
2017-01-22 Swapped WIFI_EN with SW_A to avoid interrupt sharing.
2017-01-23 Added a PTC fuse. #59.
2017-01-23 Added transient voltage suppressor to USB_VCC. Closes #59.
2017-01-23 Added 100k pullup resistors to the USART1 lines. Closes #26.
2017-01-23 Added circuitry to alow PC1 to put BOOT0 into bootloader mode. I also had to switch around SW_E from normally high to normally low.
2017-01-24 Updated PC1_BOOT0 net name.
2017-01-24 Added solder jumper to select between USB high-speed/full-speed and USB low speed. Closes #55
2017-01-24 Made Cortex header pads a bit larger. CLoses #73.
2017-01-24 Added doc layer pin 1 indicator on the debug header in library. Closes #90
2017-01-24 Changed board top edge; extended 24 mil, created protrusion to lock in with top panel of enclosure. Closes #97.
2017-01-24 Added 2x2 right angle header to board. Closes #105.
2017-01-25 Moved to ESP-09 WiFi modules. Still some work to be done.
2017-01-25 Added pin interrupt info to a page on the pin-map spreadsheet. Changed RTC battery to a CR1025. CR1025 connections still need to be routed.
2017-01-26 Routed the RTC battery. Bumped a bunch of traces around.
2017-01-27 PC4 is now VBUS_DETECT. Removed unnecessary USB data series resistors. Closes #76.'
2017-01-27 Added SPI pullups. Need to route.
2017-01-28 Added GND label to GND hook. Closes #83.
2017-01-28 Added MCU locating text. Closes #92.
2017-01-28 Added pullups to the SD interface. Closes #24.
2017-01-31 Added and LED on LCD_BL for testing.
2017-02-02 Added battery fuel gauge. Still need to route board. Closes #121.
2017-02-02 Added quto power switching. Need to route. See #118.

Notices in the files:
parts and their libraries:
SparkFun-Connectors: Licensing: Creative Commons ShareAlike 4.0 International - https://creativecommons.org/licenses/by-sa/4.0
SparkFun-Passives: Licensing: CC v3.0 Share-Alike You are welcome to use this library for commercial purposes.
